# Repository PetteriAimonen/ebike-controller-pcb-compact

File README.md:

Custom E-bike controller based on VESC 4.10
===========================================

Customized version of [Benjamin Vedder's VESC](https://github.com/vedderb/bldc-hardware) for driving BLDC motors.

VESC Hardware is licensed under the Creative Commons Attribution-ShareAlike 4.0 International License. To view a copy of this license, visit http://creativecommons.org/licenses/by-sa/4.0/.

Can use either VESC firmware or my [custom firmware](https://github.com/PetteriAimonen/ebike-controller/).

Changes:

* Added screw terminals for power cables and 2.54 mm pin headers for signals.
* Most parts are on single-side, with parts available on JLCPCB.
* Added LSM6DS3 accelerometer on board for controlling assist power
* Designed for max. 20A 50V operation.

[Schematic](design/images/BLDC_4.pdf)

Designed to mount on an aluminum block for cooling the FETs.
Alternatively a heatsink can be screwed on.

Assembly costs for 5 pcs at JLCPCB as of 2023:

    PCB (with 1 oz inner layer copper and lead-free HASL): $28.00
    Setup fee:$7.88
    Stencil:$1.48
    Components:$97.77
    Extended components fee:$29.56
    SMT Assembly:$3.43

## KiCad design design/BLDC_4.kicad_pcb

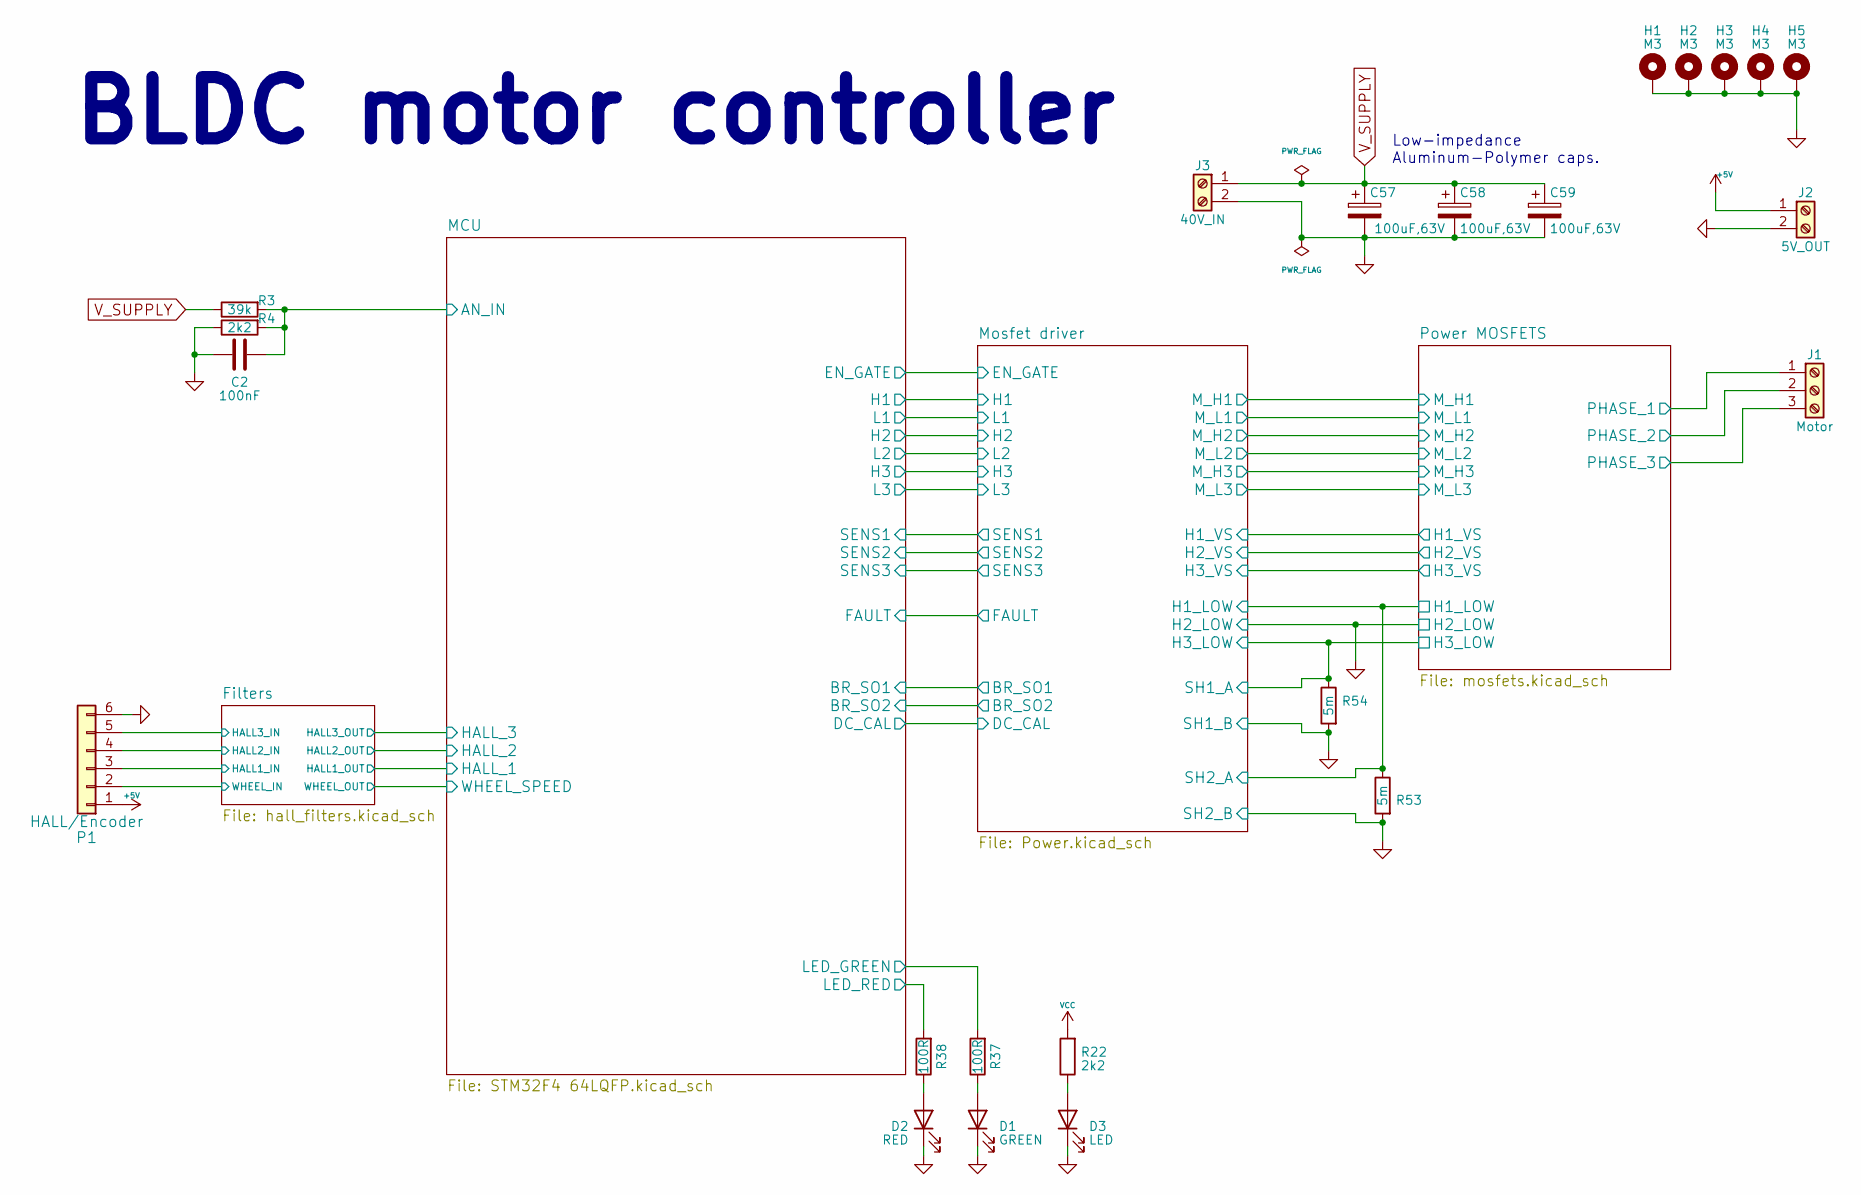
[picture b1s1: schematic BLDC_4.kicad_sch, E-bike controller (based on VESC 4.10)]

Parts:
C2: 100nF; C_0603_1608Metric; JLCPCB C14663
C57, C58, C59: 100uF,63V; CP_Elec_10x10.5; JLCPCB N/A
D1: GREEN; LED_0603_1608Metric; JLCPCB N/A
D2: RED; LED_0603_1608Metric; JLCPCB N/A
D3: LED; LED_0603_1608Metric; JLCPCB N/A
H1, H2, H3, H4, H5: M3; MountingHole_3.2mm_M3_Pad; JLCPCB N/A
J1: Motor; TerminalBlock_bornier-3_P5.08mm; JLCPCB N/A
J2: 5V_OUT; TerminalBlock_bornier-2_P5.08mm; JLCPCB N/A
J3: 40V_IN; TerminalBlock_bornier-2_P5.08mm; JLCPCB N/A
P1: HALL/Encoder; PinHeader_1x06_P2.54mm_Vertical; JLCPCB N/A
R3: 39k; R_0603_1608Metric; JLCPCB C23153
R4, R22: 2k2; R_0603_1608Metric; JLCPCB C4190
R37, R38: 100R; R_0603_1608Metric; JLCPCB C22775
R53, R54: 5m; R_2512_6332Metric; JLCPCB C5154719

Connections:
+5V: J2.1, P1.1; also elsewhere on the board
/Filters/HALL1_IN: P1.3; also elsewhere on the board
/Filters/HALL2_IN: P1.4; also elsewhere on the board
/Filters/HALL3_IN: P1.5; also elsewhere on the board
/Filters/WHEEL_IN: P1.2; also elsewhere on the board
/MCU/AN_IN: C2.2, R3.2, R4.2; also elsewhere on the board
/MCU/LED_GREEN: R37.2; also elsewhere on the board
/MCU/LED_RED: R38.2; also elsewhere on the board
/Mosfet driver/H1_LOW: R53.1; also elsewhere on the board
/Mosfet driver/H1_VS: J1.1; also elsewhere on the board
/Mosfet driver/H2_VS: J1.2; also elsewhere on the board
/Mosfet driver/H3_LOW: R54.1; also elsewhere on the board
/Mosfet driver/H3_VS: J1.3; also elsewhere on the board
GND: C2.1, C57.2, C58.2, C59.2, D1.1 (K), D2.1 (K), D3.1 (K), H1.1, H2.1, H3.1, H4.1, H5.1, J2.2, J3.2, P1.6, R4.1, R53.2, R54.2; also elsewhere on the board
unnamed: D1.2 (A), R37.1
unnamed: D2.2 (A), R38.1
unnamed: D3.2 (A), R22.1
VCC: R22.2; also elsewhere on the board
V_SUPPLY: C57.1, C58.1, C59.1, J3.1, R3.1; also elsewhere on the board

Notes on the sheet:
Low-impedance Aluminum-Polymer caps.
BLDC motor controller

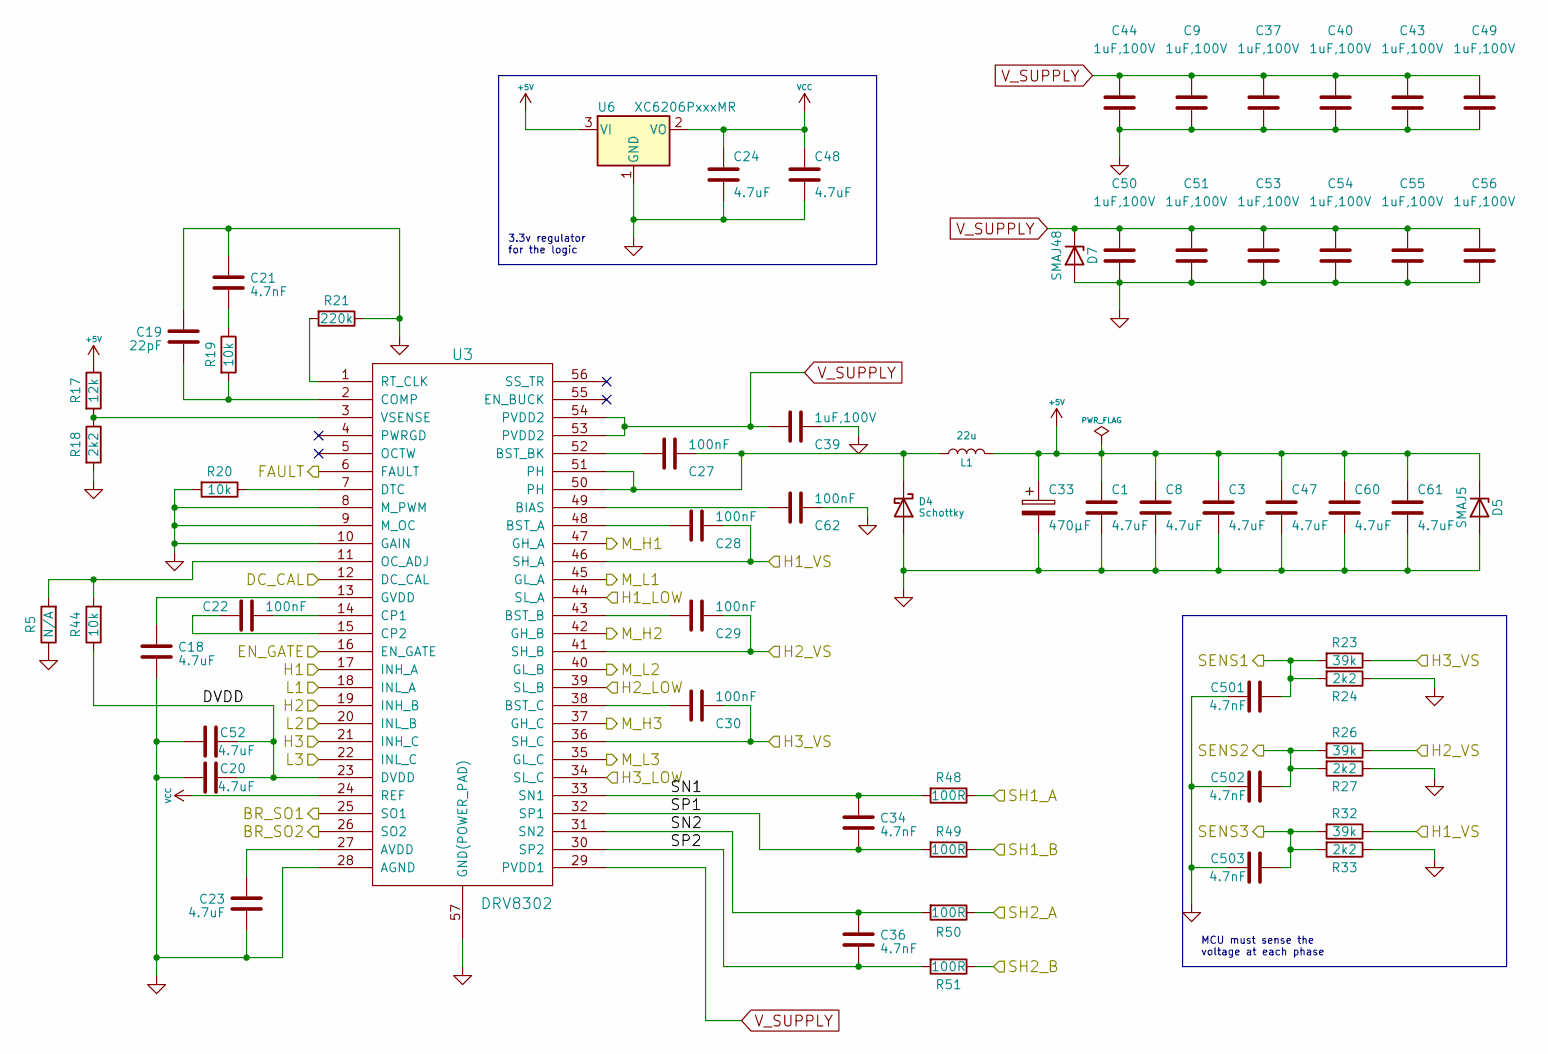
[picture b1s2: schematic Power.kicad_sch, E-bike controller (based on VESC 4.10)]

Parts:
C1, C3, C8, C18, C20, C23, C24, C47, C48, C52, C60, C61: 4.7uF; C_0603_1608Metric; JLCPCB C19666
C9, C37, C39, C40, C43, C44, C49, C50, C51, C53, C54, C55, C56: 1uF,100V; C_1206_3216Metric; JLCPCB C354362
C19: 22pF; C_0603_1608Metric; JLCPCB C1653
C21, C34, C36, C501, C502, C503: 4.7nF; C_0603_1608Metric; JLCPCB C53987
C22, C27, C28, C29, C30, C62: 100nF; C_0603_1608Metric; JLCPCB C14663
C33: 470µF; CP_Elec_10x10.5; JLCPCB N/A
D4: Schottky; D_SMA; JLCPCB C14996
D5: SMAJ5; D_SMA; JLCPCB C2925443
D7: SMAJ48; D_SMA; JLCPCB C151245
L1: 22u; L_7.3x7.3_H4.5; JLCPCB C2839926
R5: N/A; R_0603_1608Metric; JLCPCB N/A
R17: 12k; R_0603_1608Metric; JLCPCB C22790
R18, R24, R27, R33: 2k2; R_0603_1608Metric; JLCPCB C4190
R19, R20, R44: 10k; R_0603_1608Metric; JLCPCB C25804
R21: 220k; R_0603_1608Metric; JLCPCB C22961
R23, R26, R32: 39k; R_0603_1608Metric; JLCPCB C23153
R48, R49, R50, R51: 100R; R_0603_1608Metric; JLCPCB C22775
U3: DRV8302; HTSSOP-56-1EP_6.1x14mm_P0.5mm_EP3.61x6.35mm; JLCPCB C84672
U6: XC6206PxxxMR; SOT-23-3; JLCPCB C5446

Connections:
+5V: C1.1, C3.1, C8.1, C33.1, C47.1, C60.1, C61.1, D5.1 (K), L1.2, R17.1, U6.3 (VI); also elsewhere on the board
/MCU/BR_SO1: U3.25 (SO1); also elsewhere on the board
/MCU/BR_SO2: U3.26 (SO2); also elsewhere on the board
/MCU/DC_CAL: U3.12 (DC_CAL); also elsewhere on the board
/MCU/EN_GATE: U3.16 (EN_GATE); also elsewhere on the board
/MCU/FAULT: U3.6 (FAULT); also elsewhere on the board
/MCU/H1: U3.17 (INH_A); also elsewhere on the board
/MCU/H2: U3.19 (INH_B); also elsewhere on the board
/MCU/H3: U3.21 (INH_C); also elsewhere on the board
/MCU/L1: U3.18 (INL_A); also elsewhere on the board
/MCU/L2: U3.20 (INL_B); also elsewhere on the board
/MCU/L3: U3.22 (INL_C); also elsewhere on the board
/MCU/SENS1: C501.2, R23.2, R24.2; also elsewhere on the board
/MCU/SENS2: C502.2, R26.2, R27.2; also elsewhere on the board
/MCU/SENS3: C503.2, R32.2, R33.2; also elsewhere on the board
/Mosfet driver/DVDD: C20.2, C52.2, R44.1, U3.23 (DVDD)
/Mosfet driver/H1_LOW: R50.1, U3.44 (SL_A); also elsewhere on the board
/Mosfet driver/H1_VS: C28.1, R32.1, U3.46 (SH_A); also elsewhere on the board
/Mosfet driver/H2_VS: C29.1, R26.1, U3.41 (SH_B); also elsewhere on the board
/Mosfet driver/H3_LOW: R48.1, U3.34 (SL_C); also elsewhere on the board
/Mosfet driver/H3_VS: C30.1, R23.1, U3.36 (SH_C); also elsewhere on the board
/Mosfet driver/M_H1: U3.47 (GH_A); also elsewhere on the board
/Mosfet driver/M_H2: U3.42 (GH_B); also elsewhere on the board
/Mosfet driver/M_H3: U3.37 (GH_C); also elsewhere on the board
/Mosfet driver/M_L1: U3.45 (GL_A); also elsewhere on the board
/Mosfet driver/M_L2: U3.40 (GL_B); also elsewhere on the board
/Mosfet driver/M_L3: U3.35 (GL_C); also elsewhere on the board
/Mosfet driver/SN1: C34.1, R48.2, U3.33 (SN1)
/Mosfet driver/SN2: C36.1, R50.2, U3.31 (SN2)
/Mosfet driver/SP1: C34.2, R49.2, U3.32 (SP1)
/Mosfet driver/SP2: C36.2, R51.2, U3.30 (SP2)
GND: C1.2, C3.2, C8.2, C9.2, C18.2, C19.1, C20.1, C21.1, C23.1, C24.2, C33.2, C37.2, C39.1, C40.2, C43.2, C44.2, C47.2, C48.2, C49.2, C50.2, C51.2, C52.1, C53.2, C54.2, C55.2, C56.2, C60.2, C61.2, C62.1, C501.1, C502.1, C503.1, D4.2 (A), D5.2 (A), D7.2 (A), R5.1, R18.2, R20.2, R21.1, R24.1, R27.1, R33.1, R49.1, R51.1, U3.8 (M_PWM), U3.9 (M_OC), U3.10 (GAIN), U3.28 (AGND), U3.39 (SL_B), U3.57 (GND(POWER_PAD)), U6.1 (GND); also elsewhere on the board
unnamed: C21.2, R19.1
unnamed: C27.1, D4.1 (K), L1.1, U3.50 (PH), U3.51 (PH)
unnamed: C23.2, U3.27 (AVDD)
unnamed: C62.2, U3.49 (BIAS)
unnamed: C28.2, U3.48 (BST_A)
unnamed: C29.2, U3.43 (BST_B)
unnamed: C27.2, U3.52 (BST_BK)
unnamed: C30.2, U3.38 (BST_C)
unnamed: C19.2, R19.2, U3.2 (COMP)
unnamed: C22.1, U3.14 (CP1)
unnamed: C22.2, U3.15 (CP2)
unnamed: R20.1, U3.7 (DTC)
unnamed: C18.1, U3.13 (GVDD)
unnamed: R5.2, R44.2, U3.11 (OC_ADJ)
unnamed: R21.2, U3.1 (RT_CLK)
unnamed: R17.2, R18.1, U3.3 (VSENSE)
VCC: C24.1, C48.1, U3.24 (REF), U6.2 (VO); also elsewhere on the board
V_SUPPLY: C9.1, C37.1, C39.2, C40.1, C43.1, C44.1, C49.1, C50.1, C51.1, C53.1, C54.1, C55.1, C56.1, D7.1 (K), U3.29 (PVDD1), U3.53 (PVDD2), U3.54 (PVDD2); also elsewhere on the board

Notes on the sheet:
MCU must sense the voltage at each phase
3.3v regulator for the logic

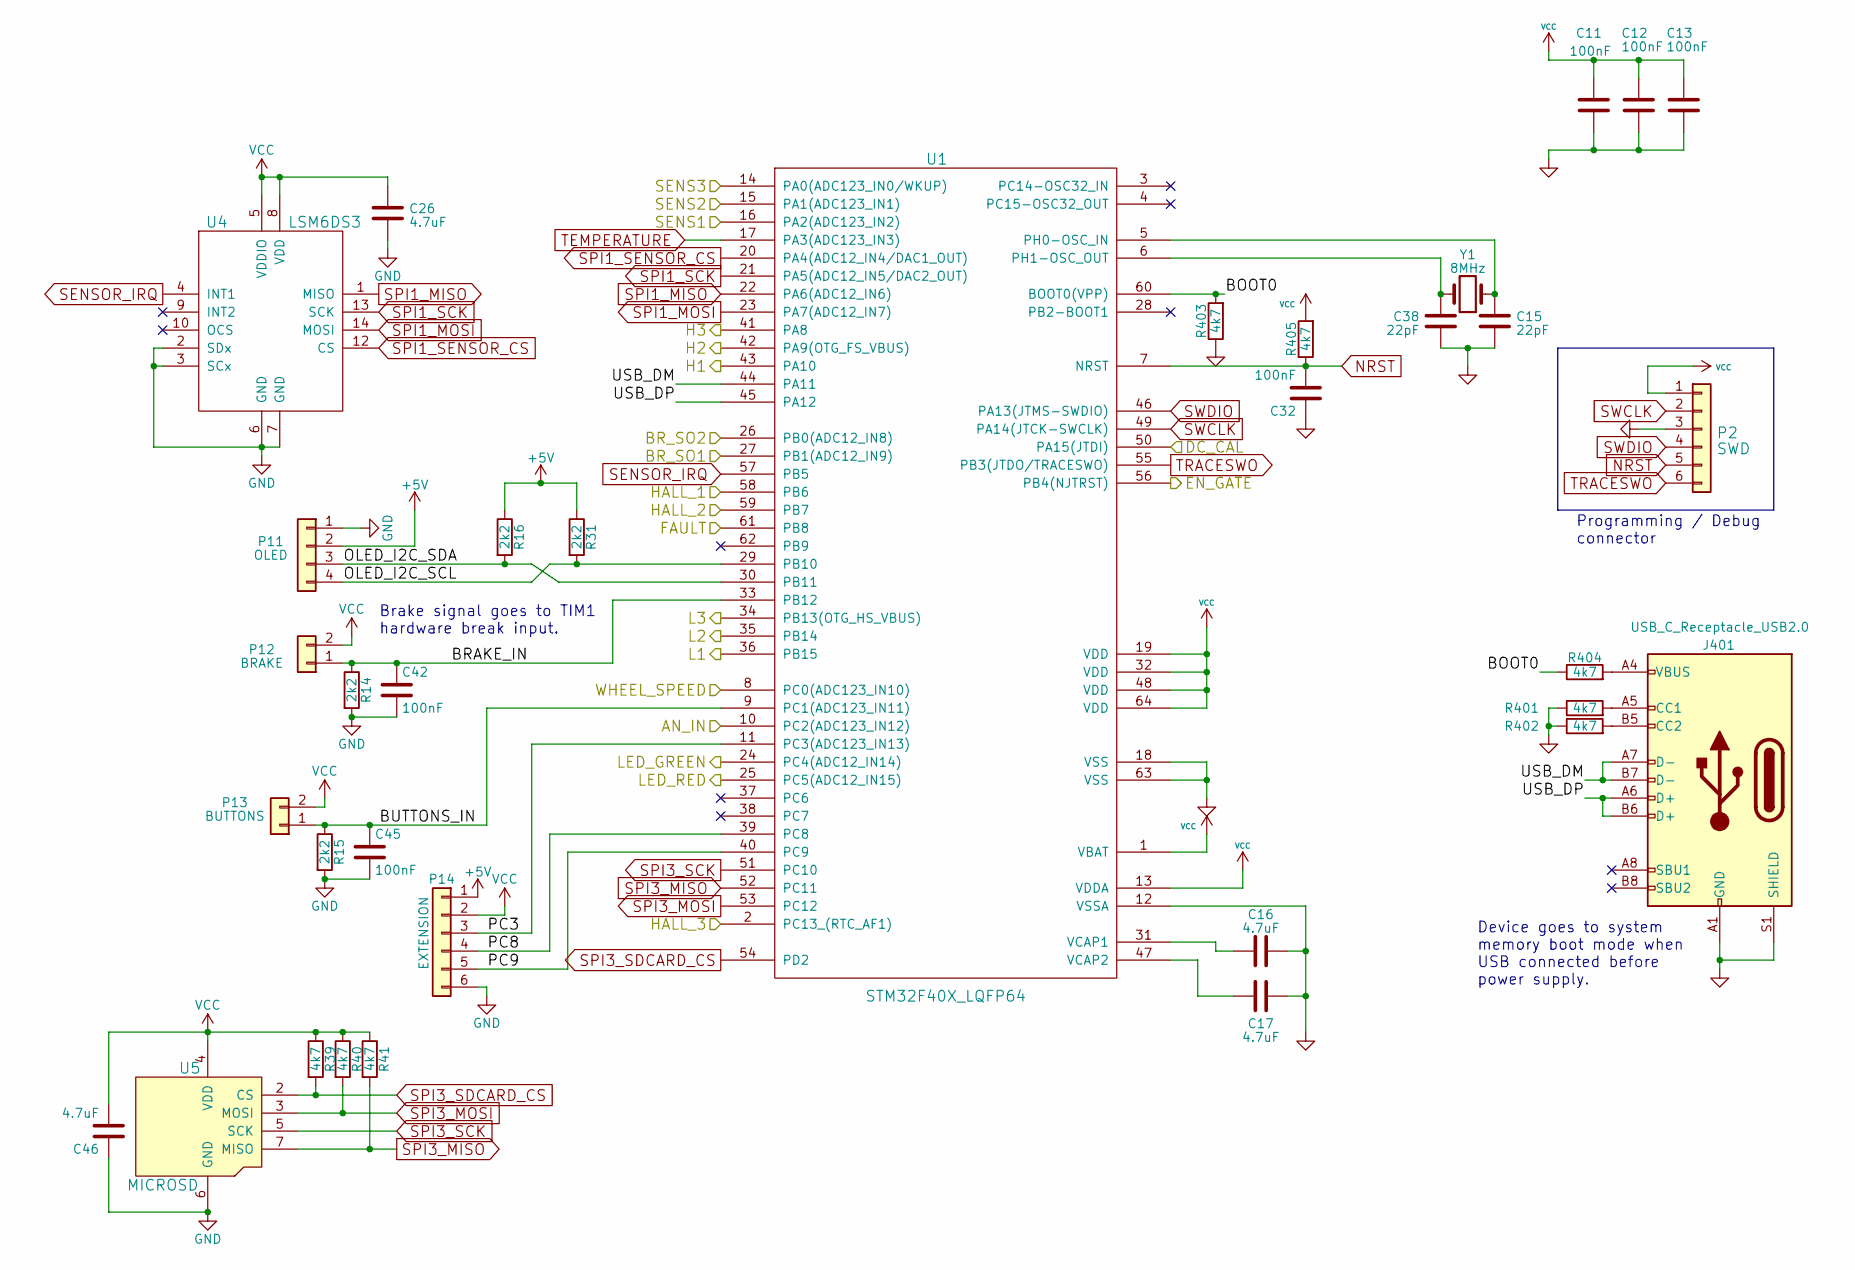
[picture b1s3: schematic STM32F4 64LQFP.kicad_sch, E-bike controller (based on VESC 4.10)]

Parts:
C11, C12, C13, C32, C42, C45: 100nF; C_0603_1608Metric; JLCPCB C14663
C15, C38: 22pF; C_0603_1608Metric; JLCPCB C1653
C16, C17, C26, C46: 4.7uF; C_0603_1608Metric; JLCPCB C19666
J401: USB_C_Receptacle_USB2.0; USB_C_Receptacle_XKB_U262-16XN-4BVC11; JLCPCB C319148
P2: SWD; PinHeader_1x06_P2.54mm_Vertical; JLCPCB N/A
P11: OLED; PinHeader_1x04_P2.54mm_Vertical; JLCPCB N/A
P12: BRAKE; PinHeader_1x02_P2.54mm_Vertical; JLCPCB N/A
P13: BUTTONS; PinHeader_1x02_P2.54mm_Vertical; JLCPCB N/A
P14: EXTENSION; PinHeader_1x06_P2.54mm_Vertical; JLCPCB N/A
R14, R15, R16, R31: 2k2; R_0603_1608Metric; JLCPCB C4190
R39, R40, R41, R401, R402, R403, R404, R405: 4k7; R_0603_1608Metric; JLCPCB C23162
U1: STM32F40X_LQFP64; LQFP-64_10x10mm_P0.5mm; JLCPCB C15742
U4: LSM6DS3; JLCPCB C967633
U5: MICROSD; microSD_HC_Molex_104031-0811; JLCPCB N/A
Y1: 8MHz; Crystal_SMD_5032-2Pin_5.0x3.2mm; JLCPCB C115962

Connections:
+5V: P11.2, P14.1, R16.1, R31.1; also elsewhere on the board
/Filters/HALL1_OUT: U1.58 (PB6); also elsewhere on the board
/Filters/HALL2_OUT: U1.59 (PB7); also elsewhere on the board
/Filters/HALL3_OUT: U1.2 (PC13_(RTC_AF1)); also elsewhere on the board
/Filters/WHEEL_OUT: U1.8 (PC0(ADC123_IN10)); also elsewhere on the board
/MCU/AN_IN: U1.10 (PC2(ADC123_IN12)); also elsewhere on the board
/MCU/BOOT0: R403.2, R404.1, U1.60 (BOOT0(VPP))
/MCU/BRAKE_IN: C42.1, P12.1, R14.1, U1.33 (PB12)
/MCU/BR_SO1: U1.27 (PB1(ADC12_IN9)); also elsewhere on the board
/MCU/BR_SO2: U1.26 (PB0(ADC12_IN8)); also elsewhere on the board
/MCU/BUTTONS_IN: C45.1, P13.1, R15.1, U1.9 (PC1(ADC123_IN11))
/MCU/DC_CAL: U1.50 (PA15(JTDI)); also elsewhere on the board
/MCU/EN_GATE: U1.56 (PB4(NJTRST)); also elsewhere on the board
/MCU/FAULT: U1.61 (PB8); also elsewhere on the board
/MCU/H1: U1.43 (PA10); also elsewhere on the board
/MCU/H2: U1.42 (PA9(OTG_FS_VBUS)); also elsewhere on the board
/MCU/H3: U1.41 (PA8); also elsewhere on the board
/MCU/L1: U1.36 (PB15); also elsewhere on the board
/MCU/L2: U1.35 (PB14); also elsewhere on the board
/MCU/L3: U1.34 (PB13(OTG_HS_VBUS)); also elsewhere on the board
/MCU/LED_GREEN: U1.24 (PC4(ADC12_IN14)); also elsewhere on the board
/MCU/LED_RED: U1.25 (PC5(ADC12_IN15)); also elsewhere on the board
/MCU/OLED_I2C_SCL: P11.4, R31.2, U1.29 (PB10)
/MCU/OLED_I2C_SDA: P11.3, R16.2, U1.30 (PB11)
/MCU/PC3: P14.3, U1.11 (PC3(ADC123_IN13))
/MCU/PC8: P14.4, U1.39 (PC8)
/MCU/PC9: P14.5, U1.40 (PC9)
/MCU/SENS1: U1.16 (PA2(ADC123_IN2)); also elsewhere on the board
/MCU/SENS2: U1.15 (PA1(ADC123_IN1)); also elsewhere on the board
/MCU/SENS3: U1.14 (PA0(ADC123_IN0/WKUP)); also elsewhere on the board
/MCU/USB_DM: J401.A7 (D-), J401.B7 (D-), U1.44 (PA11)
/MCU/USB_DP: J401.A6 (D+), J401.B6 (D+), U1.45 (PA12)
GND: C11.1, C12.1, C13.1, C15.2, C16.2, C17.2, C26.1, C32.1, C38.2, C42.2, C45.2, C46.1, J401.A1 (GND), J401.A12 (GND), J401.B1 (GND), J401.B12 (GND), J401.S1 (SHIELD), P2.3, P11.1, P14.6, R14.2, R15.2, R401.1, R402.1, R403.1, U1.12 (VSSA), U1.18 (VSS), U1.63 (VSS), U4.2 (SDx), U4.3 (SCx), U4.6 (GND), U4.7 (GND), U5.6 (GND); also elsewhere on the board
NRST: C32.2, P2.5, R405.1, U1.7 (NRST)
unnamed: J401.A5 (CC1), R401.2
unnamed: J401.B5 (CC2), R402.2
unnamed: J401.A4 (VBUS), J401.A9 (VBUS), J401.B4 (VBUS), J401.B9 (VBUS), R404.2
unnamed: C15.1, U1.5 (PH0-OSC_IN), Y1.1
unnamed: C38.1, U1.6 (PH1-OSC_OUT), Y1.2
unnamed: C16.1, U1.31 (VCAP1)
unnamed: C17.1, U1.47 (VCAP2)
SENSOR_IRQ: U1.57 (PB5), U4.4 (INT1)
SPI1_MISO: U1.22 (PA6(ADC12_IN6)), U4.1 (MISO)
SPI1_MOSI: U1.23 (PA7(ADC12_IN7)), U4.14 (MOSI)
SPI1_SCK: U1.21 (PA5(ADC12_IN5/DAC2_OUT)), U4.13 (SCK)
SPI1_SENSOR_CS: U1.20 (PA4(ADC12_IN4/DAC1_OUT)), U4.12 (CS)
SPI3_MISO: R41.2, U1.52 (PC11), U5.7 (MISO)
SPI3_MOSI: R40.2, U1.53 (PC12), U5.3 (MOSI)
SPI3_SCK: U1.51 (PC10), U5.5 (SCK)
SPI3_SDCARD_CS: R39.2, U1.54 (PD2), U5.2 (CS)
SWCLK: P2.2, U1.49 (PA14(JTCK-SWCLK))
SWDIO: P2.4, U1.46 (PA13(JTMS-SWDIO))
TEMPERATURE: U1.17 (PA3(ADC123_IN3)); also elsewhere on the board
TRACESWO: P2.6, U1.55 (PB3(JTDO/TRACESWO))
VCC: C11.2, C12.2, C13.2, C26.2, C46.2, P2.1, P12.2, P13.2, P14.2, R39.1, R40.1, R41.1, R405.2, U1.1 (VBAT), U1.13 (VDDA), U1.19 (VDD), U1.32 (VDD), U1.48 (VDD), U1.64 (VDD), U4.5 (VDDIO), U4.8 (VDD), U5.4 (VDD); also elsewhere on the board

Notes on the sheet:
Brake signal goes to TIM1 hardware break input.
Programming / Debug connector
Device goes to system memory boot mode when USB connected before power supply.

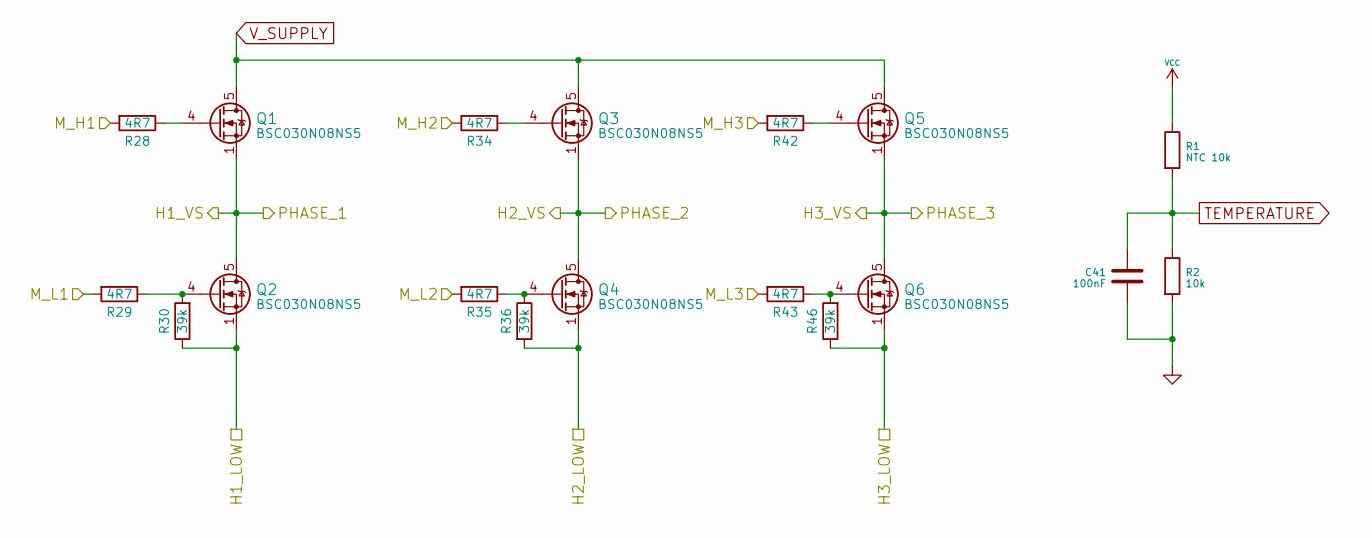
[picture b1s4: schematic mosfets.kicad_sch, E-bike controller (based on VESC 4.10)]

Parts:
C41: 100nF; C_0603_1608Metric; JLCPCB C14663
Q1, Q2, Q3, Q4, Q5, Q6: BSC030N08NS5; TDSON-8-1; JLCPCB C501507
R1: NTC 10k; R_0603_1608Metric; JLCPCB C162670
R2: 10k; R_0603_1608Metric; JLCPCB C25804
R28, R29, R34, R35, R42, R43: 4R7; R_0603_1608Metric; JLCPCB C23164
R30, R36, R46: 39k; R_0603_1608Metric; JLCPCB C23153

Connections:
/Mosfet driver/H1_LOW: Q2.1 (S), Q2.2 (S), Q2.3 (S), R30.1; also elsewhere on the board
/Mosfet driver/H1_VS: Q1.1 (S), Q1.2 (S), Q1.3 (S), Q2.5 (D); also elsewhere on the board
/Mosfet driver/H2_VS: Q3.1 (S), Q3.2 (S), Q3.3 (S), Q4.5 (D); also elsewhere on the board
/Mosfet driver/H3_LOW: Q6.1 (S), Q6.2 (S), Q6.3 (S), R46.1; also elsewhere on the board
/Mosfet driver/H3_VS: Q5.1 (S), Q5.2 (S), Q5.3 (S), Q6.5 (D); also elsewhere on the board
/Mosfet driver/M_H1: R28.2; also elsewhere on the board
/Mosfet driver/M_H2: R34.2; also elsewhere on the board
/Mosfet driver/M_H3: R42.2; also elsewhere on the board
/Mosfet driver/M_L1: R29.2; also elsewhere on the board
/Mosfet driver/M_L2: R35.2; also elsewhere on the board
/Mosfet driver/M_L3: R43.2; also elsewhere on the board
GND: C41.2, Q4.1 (S), Q4.2 (S), Q4.3 (S), R2.2, R36.2; also elsewhere on the board
unnamed: Q1.4 (G), R28.1
unnamed: Q2.4 (G), R29.1, R30.2
unnamed: Q3.4 (G), R34.1
unnamed: Q4.4 (G), R35.1, R36.1
unnamed: Q5.4 (G), R42.1
unnamed: Q6.4 (G), R43.1, R46.2
TEMPERATURE: C41.1, R1.2, R2.1; also elsewhere on the board
VCC: R1.1; also elsewhere on the board
V_SUPPLY: Q1.5 (D), Q3.5 (D), Q5.5 (D); also elsewhere on the board

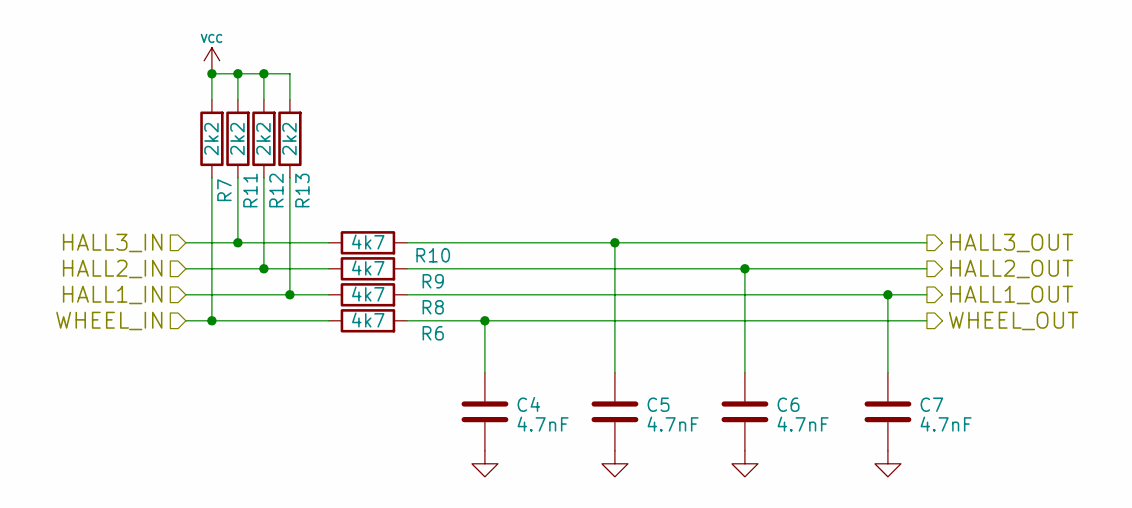
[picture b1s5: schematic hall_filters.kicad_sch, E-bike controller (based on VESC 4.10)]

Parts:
C4, C5, C6, C7: 4.7nF; C_0603_1608Metric; JLCPCB C53987
R6, R8, R9, R10: 4k7; R_0603_1608Metric; JLCPCB C23162
R7, R11, R12, R13: 2k2; R_0603_1608Metric; JLCPCB C4190

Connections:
/Filters/HALL1_IN: R8.1, R13.1; also elsewhere on the board
/Filters/HALL1_OUT: C7.1, R8.2; also elsewhere on the board
/Filters/HALL2_IN: R9.1, R12.1; also elsewhere on the board
/Filters/HALL2_OUT: C6.1, R9.2; also elsewhere on the board
/Filters/HALL3_IN: R10.1, R11.1; also elsewhere on the board
/Filters/HALL3_OUT: C5.1, R10.2; also elsewhere on the board
/Filters/WHEEL_IN: R6.1, R7.1; also elsewhere on the board
/Filters/WHEEL_OUT: C4.2, R6.2; also elsewhere on the board
GND: C4.1, C5.2, C6.2, C7.2; also elsewhere on the board
VCC: R7.2, R11.2, R12.2, R13.2; also elsewhere on the board

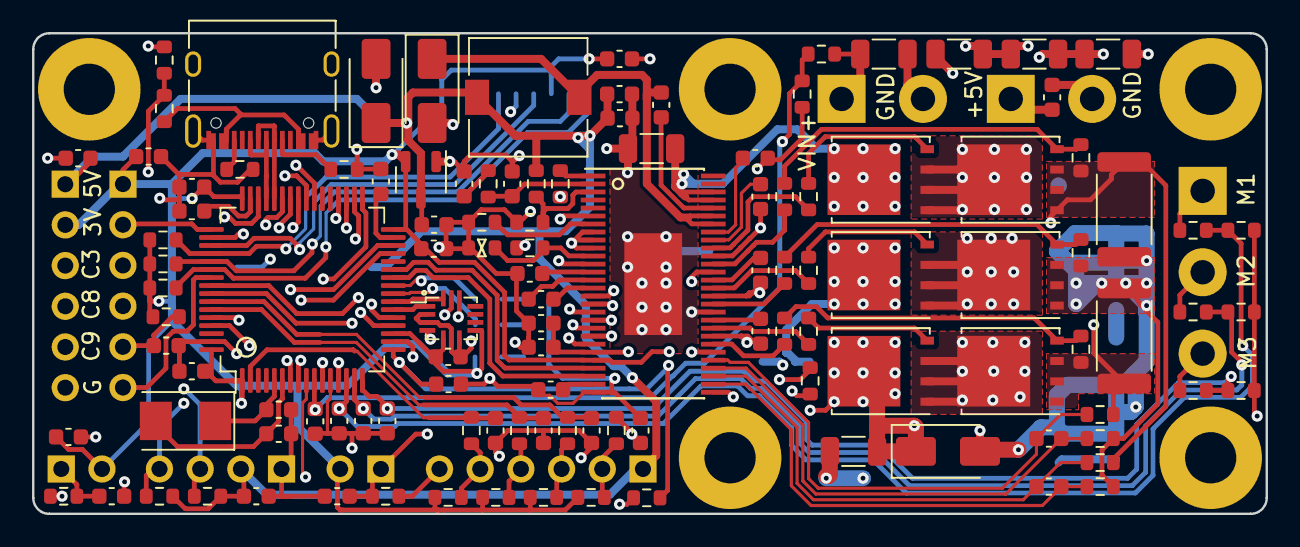
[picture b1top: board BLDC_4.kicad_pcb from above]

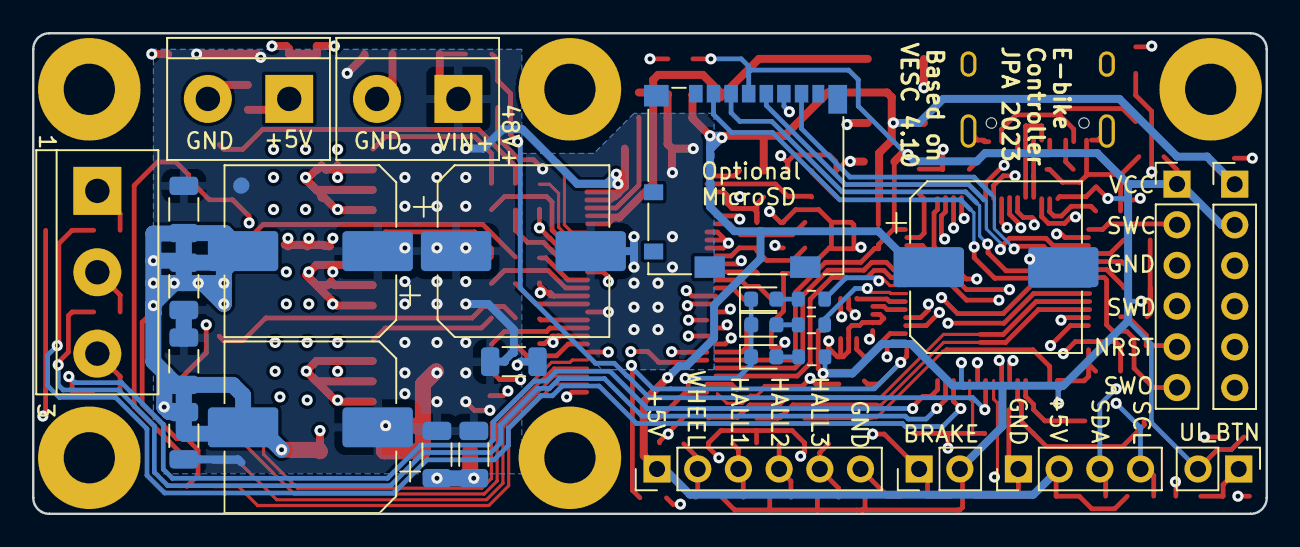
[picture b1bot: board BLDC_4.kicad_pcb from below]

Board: 4 copper layers, 77.0 x 30.0 mm, 149 parts (27 on the bottom side), 101 nets.

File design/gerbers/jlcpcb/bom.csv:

Comment,Designator,Footprint,LCSC
HALL/Encoder,P1,Connector_PinHeader_2.54mm:PinHeader_1x06_P2.54mm_Vertical,N/A
100nF,"C2,C11,C12,C13,C22,C27,C28,C29,C30,C32,C41,C42,C45,C62",Capacitor_SMD:C_0603_1608Metric,C14663
2k2,"R4,R7,R11,R12,R13,R14,R15,R16,R18,R22,R24,R27,R31,R33",Resistor_SMD:R_0603_1608Metric,C4190
39k,"R3,R23,R26,R30,R32,R36,R46",Resistor_SMD:R_0603_1608Metric,C23153
5m,"R53,R54",Resistor_SMD:R_2512_6332Metric,C5154719
100R,"R37,R38,R48,R49,R50,R51",Resistor_SMD:R_0603_1608Metric,C22775
RED,D2,LED_SMD:LED_0603_1608Metric,N/A
GREEN,D1,LED_SMD:LED_0603_1608Metric,N/A
LED,D3,LED_SMD:LED_0603_1608Metric,N/A
40V_IN,J3,TerminalBlock:TerminalBlock_bornier-2_P5.08mm,N/A
"100uF,63V","C57,C58,C59",Capacitor_SMD:CP_Elec_10x10.5,N/A
Motor,J1,TerminalBlock:TerminalBlock_bornier-3_P5.08mm,N/A
5V_OUT,J2,TerminalBlock:TerminalBlock_bornier-2_P5.08mm,N/A
Schottky,D4,Diode_SMD:D_SMA,C14996
DRV8302,U3,Package_SO:HTSSOP-56-1EP_6.1x14mm_P0.5mm_EP3.61x6.35mm,C84672
22u,L1,Inductor_SMD:L_7.3x7.3_H4.5,C2839926
470µF,C33,Capacitor_SMD:CP_Elec_10x10.5,N/A
4.7uF,"C1,C3,C8,C16,C17,C18,C20,C23,C24,C26,C46,C47,C48,C52,C60,C61",Capacitor_SMD:C_0603_1608Metric,C19666
10k,"R2,R19,R20,R44",Resistor_SMD:R_0603_1608Metric,C25804
220k,R21,Resistor_SMD:R_0603_1608Metric,C22961
12k,R17,Resistor_SMD:R_0603_1608Metric,C22790
4.7nF,"C4,C5,C6,C7,C21,C34,C36,C501,C502,C503",Capacitor_SMD:C_0603_1608Metric,C53987
22pF,"C15,C19,C38",Capacitor_SMD:C_0603_1608Metric,C1653
"1uF,100V","C9,C37,C39,C40,C43,C44,C49,C50,C51,C53,C54,C55,C56",Capacitor_SMD:C_1206_3216Metric,C354362
XC6206PxxxMR,U6,Package_TO_SOT_SMD:SOT-23-3,C5446
SMAJ48,D7,Diode_SMD:D_SMA,C151245
SMAJ5,D5,Diode_SMD:D_SMA,C2925443
STM32F40X_LQFP64,U1,Package_QFP:LQFP-64_10x10mm_P0.5mm,C15742
SWD,P2,Connector_PinHeader_2.54mm:PinHeader_1x06_P2.54mm_Vertical,N/A
OLED,P11,Connector_PinHeader_2.54mm:PinHeader_1x04_P2.54mm_Vertical,N/A
BRAKE,P12,Connector_PinHeader_2.54mm:PinHeader_1x02_P2.54mm_Vertical,N/A
BUTTONS,P13,Connector_PinHeader_2.54mm:PinHeader_1x02_P2.54mm_Vertical,N/A
EXTENSION,P14,Connector_PinHeader_2.54mm:PinHeader_1x06_P2.54mm_Vertical,N/A
MICROSD,U5,Connector_Card:microSD_HC_Molex_104031-0811,N/A
LSM6DS3,U4,LSM6DS3:LSM6DS3,C967633
4k7,"R6,R8,R9,R10,R39,R40,R41,R401,R402,R403,R404,R405",Resistor_SMD:R_0603_1608Metric,C23162
USB_C_Receptacle_USB2.0,J401,Connector_USB:USB_C_Receptacle_XKB_U262-16XN-4BVC11,C319148
8MHz,Y1,Crystal:Crystal_SMD_5032-2Pin_5.0x3.2mm,C115962
BSC030N08NS5,"Q1,Q2,Q3,Q4,Q5,Q6",Package_TO_SOT_SMD:TDSON-8-1,C501507
4R7,"R28,R29,R34,R35,R42,R43",Resistor_SMD:R_0603_1608Metric,C23164
NTC 10k,R1,Resistor_SMD:R_0603_1608Metric,C162670

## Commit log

2015-10-25 Add 60V->5V buck converter and bypassing caps on board
2015-11-01 schema mods done
2023-05-22 Relayout to more compact version, update to KiCad 7
2023-06-02 Update README, add FreeCAD design of mounting
2023-06-02 Remove outdated files
2023-06-10 More mechanical parts
2023-07-14 Mechanical parts
2023-08-05 Battery holder bracket
2023-08-12 battery locking bracket
2025-03-14 ledstrip cover
2025-03-28 Slight adjustment of UI panel design
2025-03-29 Fix geometry
